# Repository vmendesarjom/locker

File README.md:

# lock3r - VMendesARJOM
# Garag3m: hub

Projeto base e integrador dos demais projetos desenvolvidos pela Garag3m.

## Apps

O projeto é composto pela aplicação *core* composta basicamente pelas classes *CreateUpdateModel* e *UUIDUser*.

### CreateUpdateModel

Classe composta basicamente pelos atributos de data de criação (created_at) e data da última atualização (updated_at). Além disso ela define o *id* como sendo um UUID.

```python
class CreateUpdateModel(models.Model):

    id = models.UUIDField(primary_key=True, default=uuid.uuid4, editable=False)
    created_at = models.DateTimeField('criado em', auto_now_add=True)
    updated_at = models.DateTimeField('atualizado em', auto_now=True)

    class Meta:
        abstract = True
```

### UUIDUser

Classe que herda da classe AbstractUser, sendo utilizada para sobrescrever a classe User do Django. Como diferencial ela possui apenas os atributos de cpf, matrícula e imagem do profile do usuário.

```python
class UUIDUser(AbstractUser):

    id = models.UUIDField(primary_key=True, default=uuid.uuid4, editable=False)
    groups = models.ManyToManyField(Group, blank=True, related_name="uuiduser_set", related_query_name="user")
    user_permissions = models.ManyToManyField(Permission, blank=True, related_name="uuiduser_set", related_query_name="user")

    # core
    cpf = models.CharField(max_length=11, null=True, blank=True, verbose_name="CPF")
    registration = models.CharField(max_length=100, null=True, blank=True, verbose_name="matrícula")

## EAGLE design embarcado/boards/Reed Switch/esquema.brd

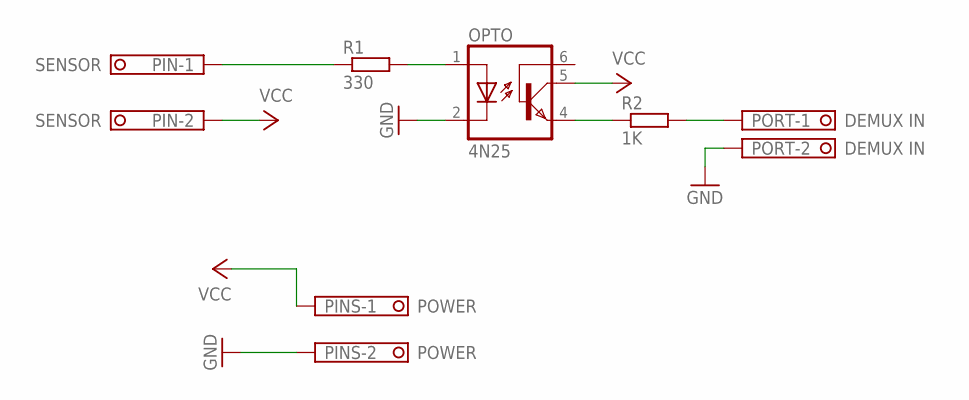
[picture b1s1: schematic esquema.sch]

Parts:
OPTO: 4N25; DIL06
PIN: SENSOR; TERMINAL-BLOCK-2-PIN-3.5MM-ROUND-PAD
PINS: POWER; TERMINAL-BLOCK-2-PIN-3.5MM-ROUND-PAD
PORT: DEMUX IN; TERMINAL-BLOCK-2-PIN-3.5MM-ROUND-PAD
R1: 330; 0204/7
R2: 1K; 0204/7

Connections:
GND: OPTO.2 (C), PINS.2, PORT.2
unnamed: OPTO.1 (A), R1.2
unnamed: OPTO.4 (EMI), R2.1
unnamed: PORT.1, R2.2
unnamed: PIN.1, R1.1
VCC: OPTO.5 (COL), PIN.2, PINS.1

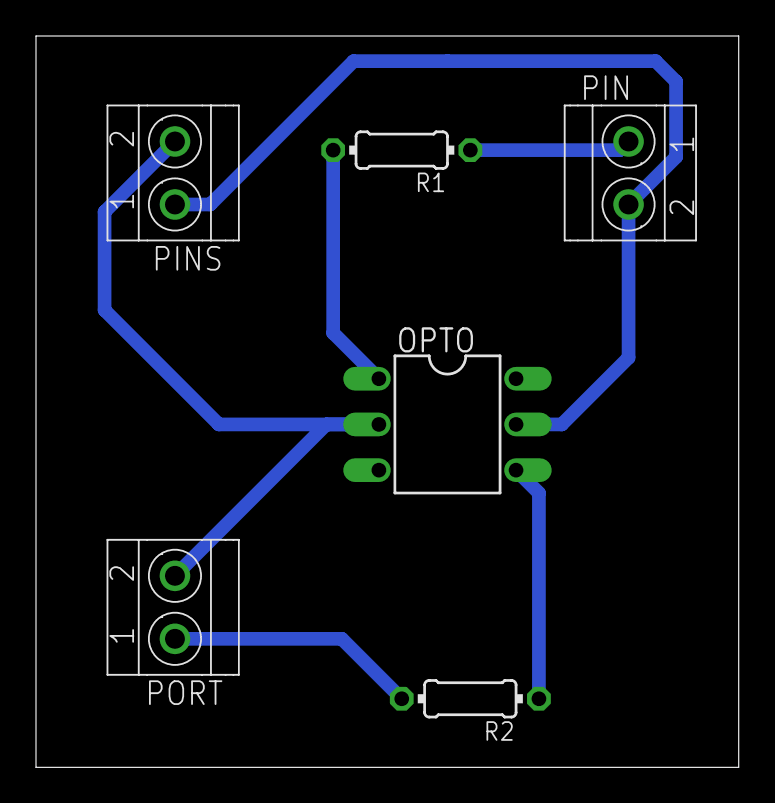
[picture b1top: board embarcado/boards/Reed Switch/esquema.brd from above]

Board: 2 copper layers, 39.0 x 40.6 mm, 6 parts (0 on the bottom side), 6 nets.

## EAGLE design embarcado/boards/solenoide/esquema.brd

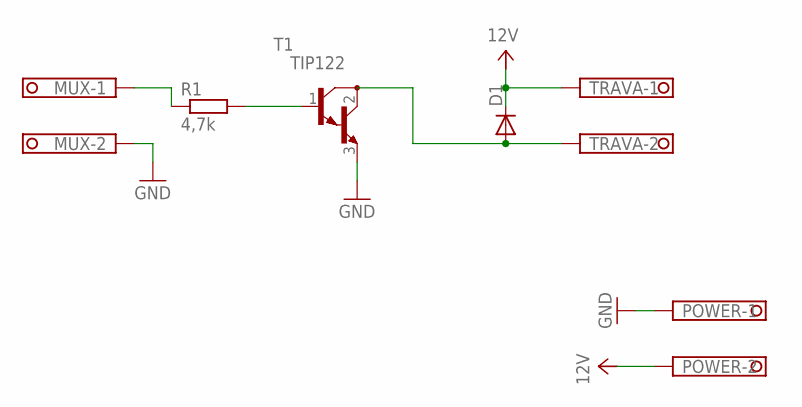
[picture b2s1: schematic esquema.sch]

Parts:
D1: 1N4004; DO41-10
MUX: TERMINAL-BLOCK-3.5MM-2-PIN-ROUND-PAD; TERMINAL-BLOCK-2-PIN-3.5MM-ROUND-PAD
POWER: TERMINAL-BLOCK-3.5MM-2-PIN-ROUND-PAD; TERMINAL-BLOCK-2-PIN-3.5MM-ROUND-PAD
R1: 4,7k; 0207/10
T1: TIP122; TO220
TRAVA: TERMINAL-BLOCK-3.5MM-2-PIN-ROUND-PAD; TERMINAL-BLOCK-2-PIN-3.5MM-ROUND-PAD

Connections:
12V: D1.C, POWER.2, TRAVA.1
GND: MUX.2, POWER.1, T1.3 (E)
unnamed: D1.A, T1.2 (C), TRAVA.2
unnamed: R1.2, T1.1 (B)
unnamed: MUX.1, R1.1

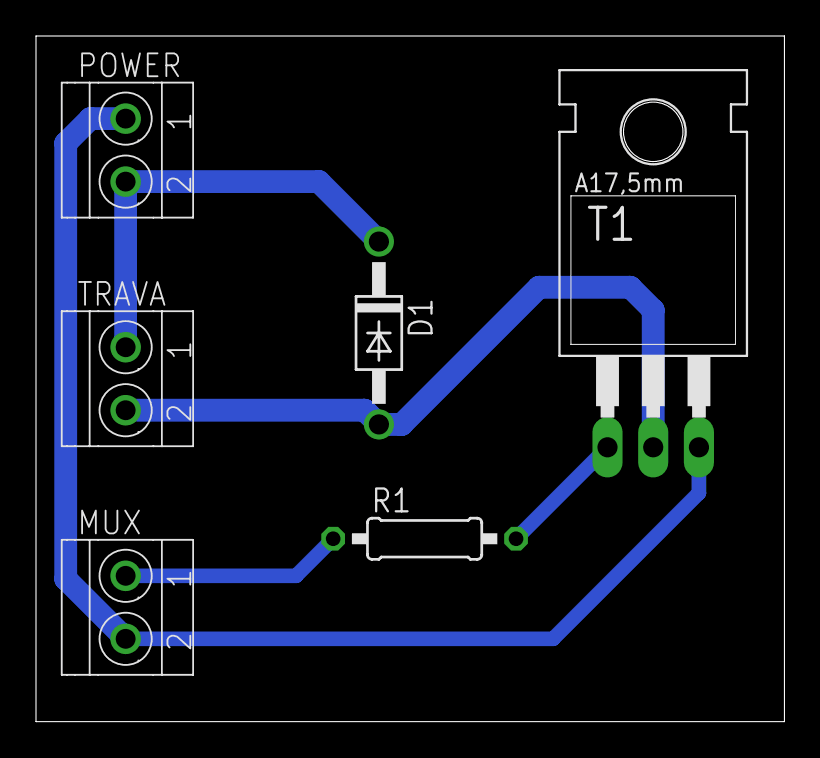
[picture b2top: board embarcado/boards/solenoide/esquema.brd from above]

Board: 2 copper layers, 41.6 x 38.1 mm, 6 parts (0 on the bottom side), 5 nets.

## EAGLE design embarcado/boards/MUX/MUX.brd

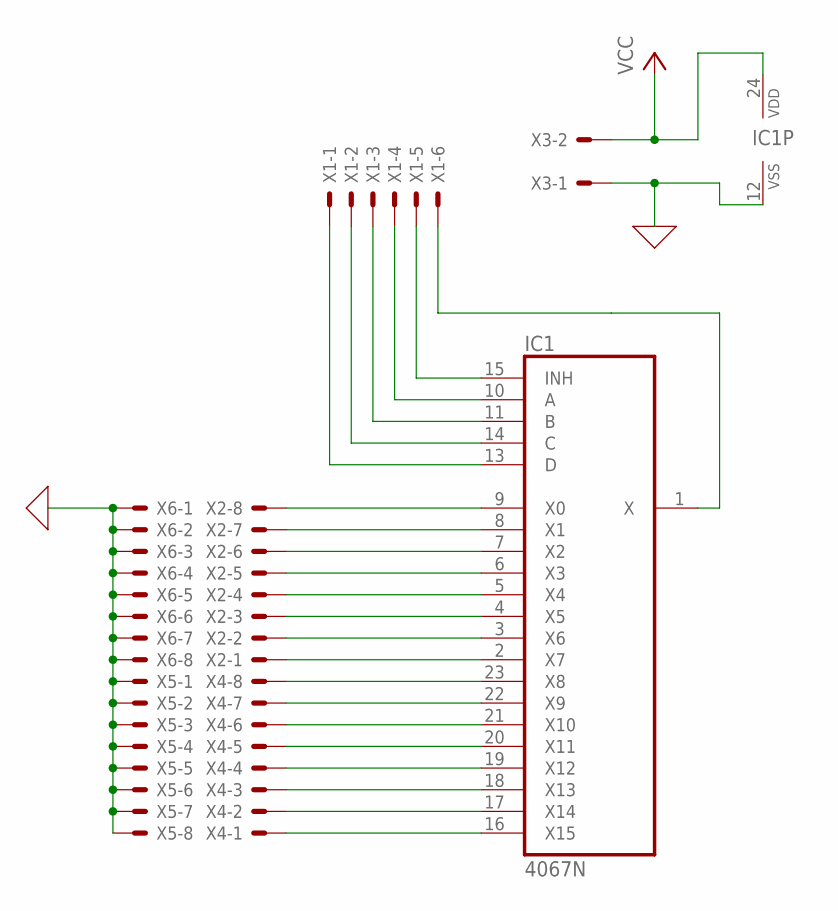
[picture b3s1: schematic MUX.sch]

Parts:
IC1: 4067N; DIL24-6
X1: KK-156-6
X2, X4, X5, X6: KK-156-8
X3: KK-156-2

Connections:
0: IC1.12 (VSS), X3.1, X5.1, X5.2, X5.3, X5.4, X5.5, X5.6, X5.7, X5.8, X6.1, X6.2, X6.3, X6.4, X6.5, X6.6, X6.7, X6.8
unnamed: IC1.9 (X0), X2.8
unnamed: IC1.8 (X1), X2.7
unnamed: IC1.7 (X2), X2.6
unnamed: IC1.6 (X3), X2.5
unnamed: IC1.5 (X4), X2.4
unnamed: IC1.4 (X5), X2.3
unnamed: IC1.3 (X6), X2.2
unnamed: IC1.2 (X7), X2.1
unnamed: IC1.23 (X8), X4.8
unnamed: IC1.22 (X9), X4.7
unnamed: IC1.21 (X10), X4.6
unnamed: IC1.20 (X11), X4.5
unnamed: IC1.19 (X12), X4.4
unnamed: IC1.18 (X13), X4.3
unnamed: IC1.17 (X14), X4.2
unnamed: IC1.16 (X15), X4.1
unnamed: IC1.13 (D), X1.1
unnamed: IC1.14 (C), X1.2
unnamed: IC1.11 (B), X1.3
unnamed: IC1.10 (A), X1.4
unnamed: IC1.15 (INH), X1.5
unnamed: IC1.1 (X), X1.6
VCC: IC1.24 (VDD), X3.2

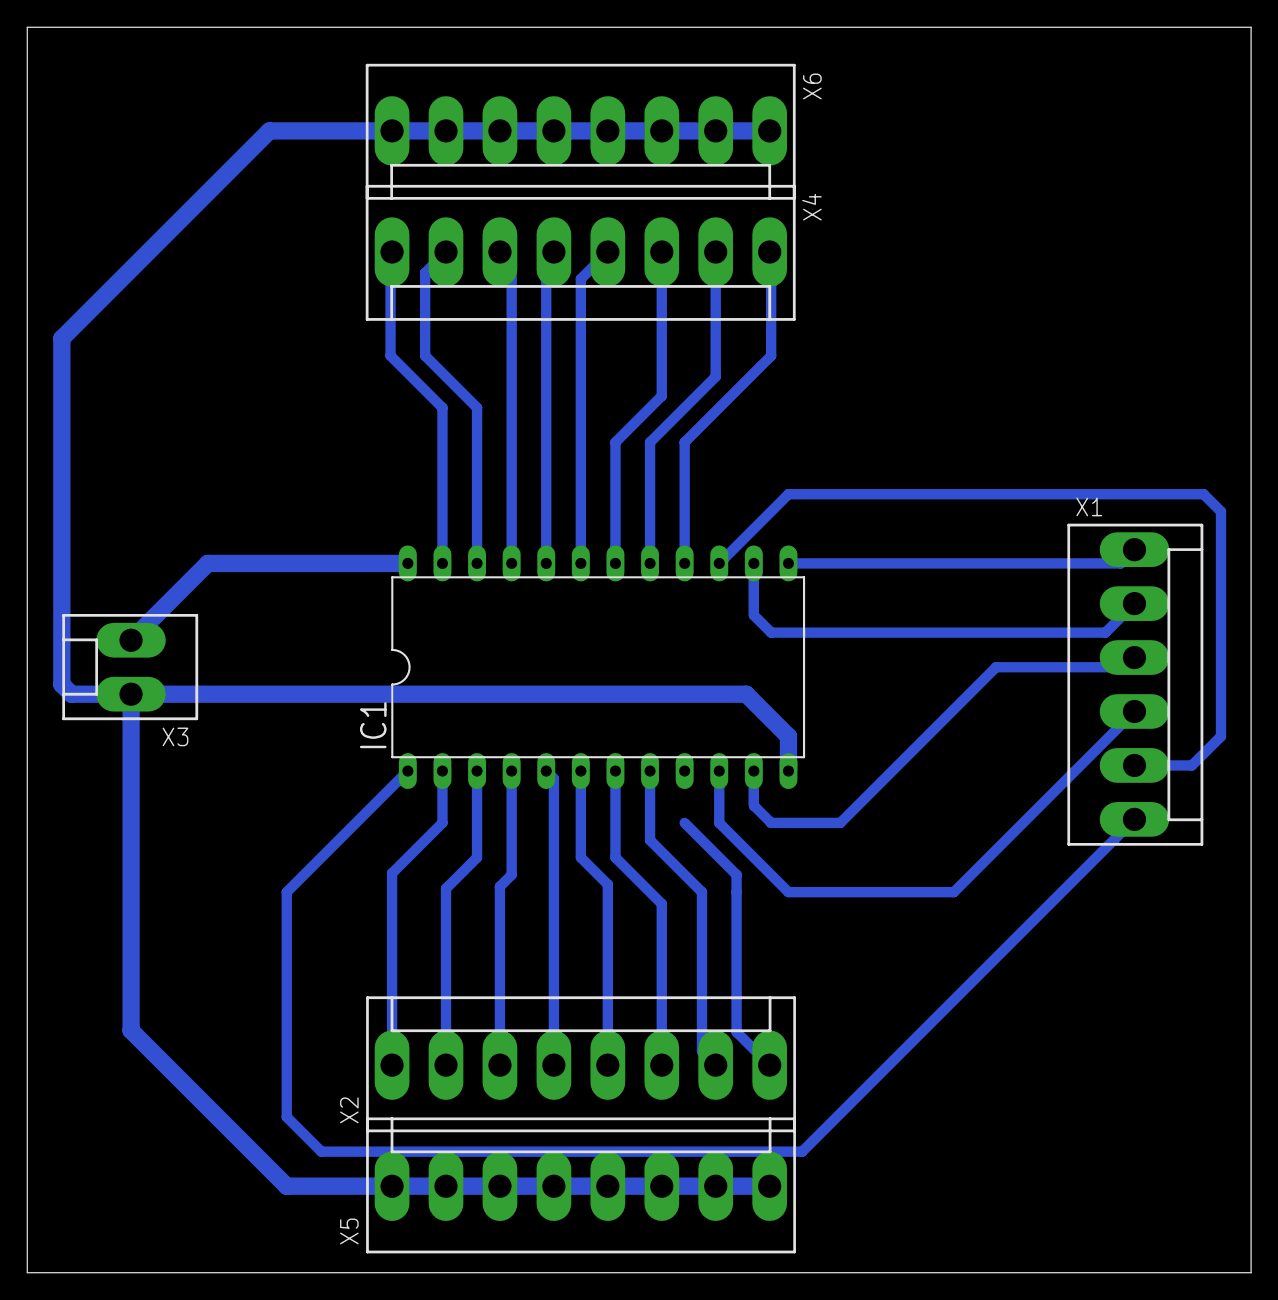
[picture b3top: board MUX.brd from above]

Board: 2 copper layers, 89.8 x 91.4 mm, 7 parts (0 on the bottom side), 24 nets.

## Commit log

2018-09-17 reserve historic & rate
2018-09-17 reserve rate
2018-09-21 historic, search & rate
2018-09-21 reserve, search and rate
2018-09-24 lock3r | rate and search
2018-10-16 embarcado
2018-10-17 lock3r | Gerar PDF
2018-10-17 lock3r | django - gerar pdf
2018-10-31 lock3r | details
